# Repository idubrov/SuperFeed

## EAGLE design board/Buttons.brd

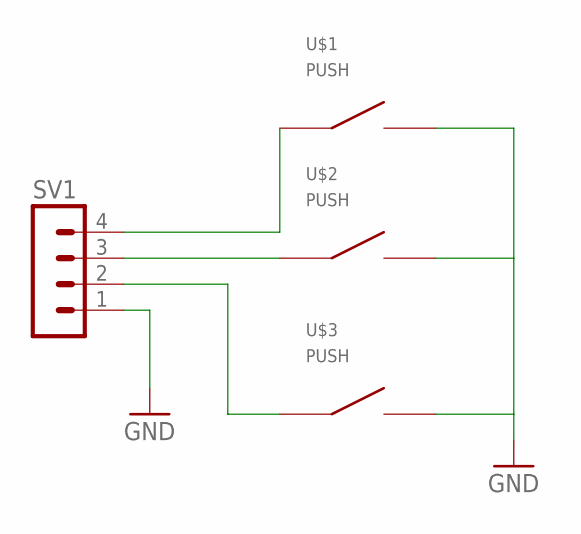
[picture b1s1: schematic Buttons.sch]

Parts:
SV1: MA04-1W
U$1, U$2, U$3: PUSH

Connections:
GND: SV1.1, U$1.3 (2), U$1.4 (2), U$2.3 (2), U$2.4 (2), U$3.3 (2), U$3.4 (2)
unnamed: SV1.2, U$3.1, U$3.2 (1)
unnamed: SV1.3, U$2.1, U$2.2 (1)
unnamed: SV1.4, U$1.1, U$1.2 (1)

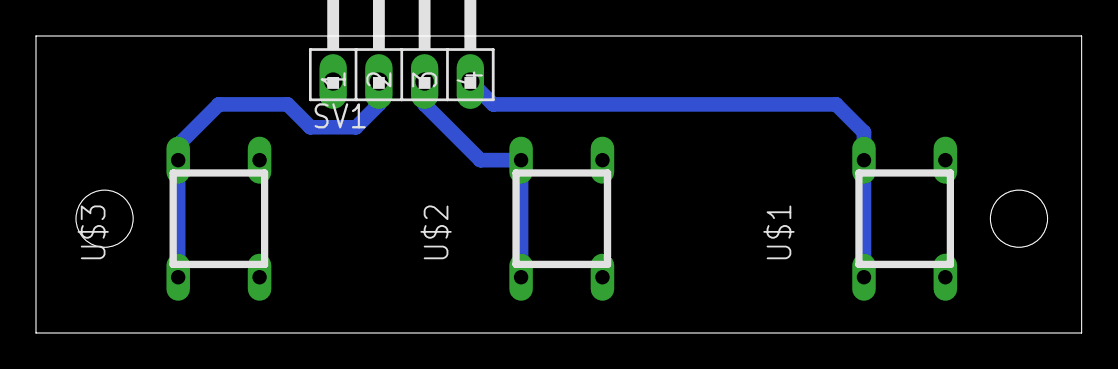
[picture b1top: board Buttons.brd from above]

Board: 2 copper layers, 58.1 x 16.5 mm, 4 parts (0 on the bottom side), 4 nets.

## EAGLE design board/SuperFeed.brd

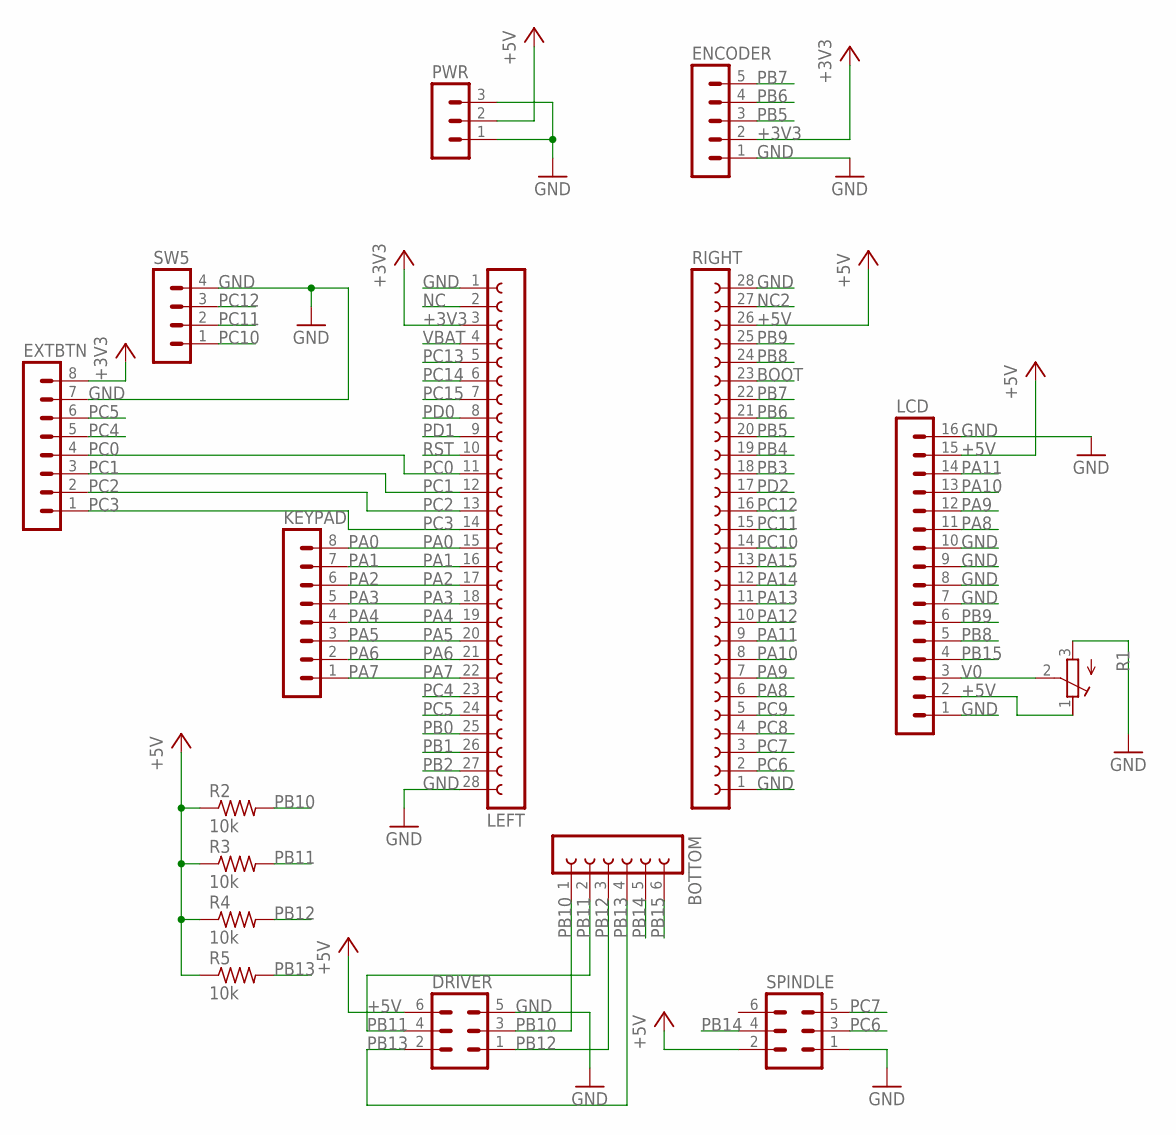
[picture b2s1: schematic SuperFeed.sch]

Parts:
BOTTOM: FE06-1; FE06
DRIVER: MA03-2W
ENCODER: MA05-1W
EXTBTN: MA08-1W
KEYPAD: MA08-1W
LCD: MA16-1
LEFT: FE28-1; FE28
PWR: MA03-1W
R1: R-TRIMMT93YA; RTRIMT93YA
R2, R3, R4, R5: 10k; 0207/10
RIGHT: FE28-1; FE28
SPINDLE: MA03-2W
SW5: MA04-1W

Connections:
+3V3: ENCODER.2, EXTBTN.8, LEFT.3
+5V: DRIVER.6, LCD.2, LCD.15, PWR.2, R1.1 (E), R2.1, R3.1, R4.1, R5.1, RIGHT.26, SPINDLE.2
BOOT: RIGHT.23
GND: DRIVER.5, ENCODER.1, EXTBTN.7, LCD.1, LCD.7, LCD.8, LCD.9, LCD.10, LCD.16, LEFT.1, LEFT.28, PWR.1, PWR.3, R1.3 (A), RIGHT.1, RIGHT.28, SPINDLE.1, SW5.4
NC: LEFT.2
NC2: RIGHT.27
PA0: KEYPAD.8, LEFT.15
PA1: KEYPAD.7, LEFT.16
PA2: KEYPAD.6, LEFT.17
PA3: KEYPAD.5, LEFT.18
PA4: KEYPAD.4, LEFT.19
PA5: KEYPAD.3, LEFT.20
PA6: KEYPAD.2, LEFT.21
PA7: KEYPAD.1, LEFT.22
PA8: LCD.11, RIGHT.6
PA9: LCD.12, RIGHT.7
PA10: LCD.13, RIGHT.8
PA11: LCD.14, RIGHT.9
PA12: RIGHT.10
PA13: RIGHT.11
PA14: RIGHT.12
PA15: RIGHT.13
PB0: LEFT.25
PB1: LEFT.26
PB2: LEFT.27
PB3: RIGHT.18
PB4: RIGHT.19
PB5: ENCODER.3, RIGHT.20
PB6: ENCODER.4, RIGHT.21
PB7: ENCODER.5, RIGHT.22
PB8: LCD.5, RIGHT.24
PB9: LCD.6, RIGHT.25
PB10: BOTTOM.1, DRIVER.3, R2.2
PB11: BOTTOM.2, DRIVER.4, R3.2
PB12: BOTTOM.3, DRIVER.1, R4.2
PB13: BOTTOM.4, DRIVER.2, R5.2
PB14: BOTTOM.5, SPINDLE.4
PB15: BOTTOM.6, LCD.4
PC0: EXTBTN.4, LEFT.11
PC1: EXTBTN.3, LEFT.12
PC2: EXTBTN.2, LEFT.13
PC3: EXTBTN.1, LEFT.14
PC4: EXTBTN.5, LEFT.23
PC5: EXTBTN.6, LEFT.24
PC6: RIGHT.2, SPINDLE.3
PC7: RIGHT.3, SPINDLE.5
PC8: RIGHT.4
PC9: RIGHT.5
PC10: RIGHT.14, SW5.1
PC11: RIGHT.15, SW5.2
PC12: RIGHT.16, SW5.3
PC13: LEFT.5
PC14: LEFT.6
PC15: LEFT.7
PD0: LEFT.8
PD1: LEFT.9
PD2: RIGHT.17
RST: LEFT.10
V0: LCD.3, R1.2 (S)
VBAT: LEFT.4

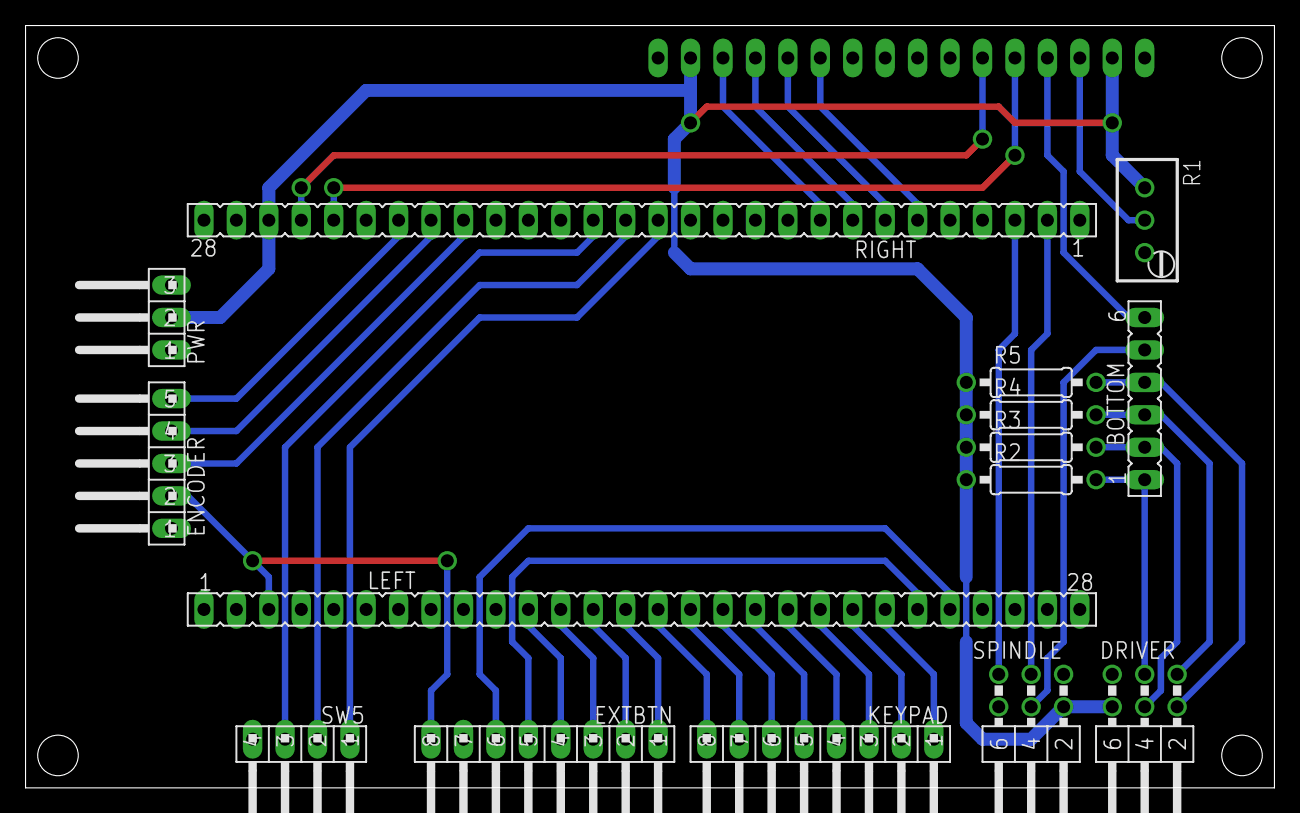
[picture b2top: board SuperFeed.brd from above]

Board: 2 copper layers, 97.8 x 59.7 mm, 16 parts (1 on the bottom side), 38 nets.

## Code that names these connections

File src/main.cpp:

#include "simstream.hpp"
#include "util.hpp"
#include "settings.hpp"

// Hardwre
#include "hw/buttons.hpp"
#include "hw/core.hpp"
#include "hw/driver.hpp"
#include "hw/eeprom.hpp"
#include "hw/encoder.hpp"
#include "hw/keypad.hpp"
#include "hw/lcd.hpp"
#include "hw/spindle.hpp"

// Text UI
#include "tui/console.hpp"
#include "tui/menu/controls.hpp"
#include "tui/menu/inputs.hpp"
#include "tui/menu/menu.hpp"
#include "tui/menu/sampler.hpp"
#include "tui/menu/limits.hpp"
#include "tui/menu/powerfeed.hpp"
#include "tui/menu/drvtest.hpp"

// Stepper
#include "stepper/stepper.hpp"

extern "C"
{
void SysTick_Handler();
void TIM1_UP_TIM16_IRQHandler(); // STEP pulse generation
void TIM7_IRQHandler(); // Input debouncing
void TIM1_BRK_TIM15_IRQHandler(); // Spindle index

extern unsigned int __eeprom_start;
extern unsigned int __eeprom_pages;
}

// First, enable clocks for utilized subsystems
class application
{
	friend void ::TIM1_UP_TIM16_IRQHandler();
	friend void ::TIM7_IRQHandler();
	friend void ::TIM1_BRK_TIM15_IRQHandler();
public:
	application() :
			// Columns start with pin PA0, rows start with PA4
			keypad(GPIOA, GPIO_PinSource0, GPIO_PinSource4),
			// PC10-PC12 should be connected to the first three output of three buttons.
			buttons(GPIOC, GPIO_PinSource10),
			// PB5 should be connected to encoder button, PB6 and PB7 to rotary encoder.
			encoder(GPIOB, TIM4, GPIO_Pin_5, GPIO_Pin_6 | GPIO_Pin_7),
			// LCD display, RS pin should be connected to PB15, R/W to PB8 and E to PB9
			// D4-D7 should be connected to PB8-PB15
			lcd(GPIOB, GPIO_Pin_15, GPIO_Pin_8, GPIO_Pin_9, GPIOA,
			GPIO_PinSource8, hw::lcd::Bit4, false),
			// Stepper driver, PB13 should be connected to STEP, PB12 to DIR,
			// PB11 to ENABLE and PB10 to RESET.
			// ENABLE and RESET are active high (i.e, driver is enabled when both are high).
			driver(GPIOB, GPIO_Pin_13, GPIO_Pin_12, GPIO_Pin_11, GPIO_Pin_10,
			TIM1),
			// Spindle index, PB14 should be connected to hall sensor or optical sensor
			spindle(TIM15,
			GPIOB, GPIO_Pin_14),
			// Use page 126 and 127 for persistent storage
			eeprom((uint32_t) &__eeprom_start, (uint32_t) &__eeprom_pages), stepper(
					eeprom, driver), console(lcd,
			TIM7, encoder, keypad, buttons), sampler(spindle), rotatetest(
					driver, stepper, eeprom)
	{
	}

	void setup()
	{
		RCC_APB2PeriphClockCmd(RCC_APB2Periph_GPIOA, ENABLE);
		RCC_APB2PeriphClockCmd(RCC_APB2Periph_GPIOB, ENABLE);
		RCC_APB2PeriphClockCmd(RCC_APB2Periph_GPIOC, ENABLE);
		RCC_APB2PeriphClockCmd(RCC_APB2Periph_TIM1, ENABLE); // Stepper
		RCC_APB2PeriphClockCmd(RCC_APB2Periph_TIM15, ENABLE); // Spindle index timer
		RCC_APB2PeriphClockCmd(RCC_APB2Periph_AFIO, ENABLE);
		RCC_APB1PeriphClockCmd(RCC_APB1Periph_TIM4, ENABLE); // Encoder
		RCC_APB1PeriphClockCmd(RCC_APB1Periph_TIM6, ENABLE); // Utility timer
		RCC_APB1PeriphClockCmd(RCC_APB1Periph_TIM7, ENABLE); // Debouncing timer

		// Remap TIM15 to use PB14 as CH1
		AFIO->MAPR2 |= AFIO_MAPR2_TIM15_REMAP;
		// XXX: The following line doesn't work with gcc optimizations
		//GPIO_PinRemapConfig(GPIO_Remap_TIM15, ENABLE);

		// Setup interrupt for pulse timer (TIM1)
		NVIC_InitTypeDef timerIT;
		timerIT.NVIC_IRQChannel = TIM1_UP_TIM16_IRQn;
		timerIT.NVIC_IRQChannelPreemptionPriority = 0;
		timerIT.NVIC_IRQChannelSubPriority = 1;
		timerIT.NVIC_IRQChannelCmd = ENABLE;
		NVIC_Init(&timerIT);

		// Setup interrupt for debounce timer (TIM7)
		timerIT.NVIC_IRQChannel = TIM7_IRQn;
		timerIT.NVIC_IRQChannelPreemptionPriority = 3; // lowest priority
		timerIT.NVIC_IRQChannelSubPriority = 3; // lowest priority
		timerIT.NVIC_IRQChannelCmd = ENABLE;
		NVIC_Init(&timerIT);

		// Setup interrupt for spindle index timer (TIM15)
		timerIT.NVIC_IRQChannel = TIM1_BRK_TIM15_IRQn;
		timerIT.NVIC_IRQChannelPreemptionPriority = 3;
		timerIT.NVIC_IRQChannelSubPriority = 2;
		timerIT.NVIC_IRQChannelCmd = ENABLE;
		NVIC_Init(&timerIT);

		// Setup core hardware (on-board LEDs and delay timer)
		hw::core::setup();

		// Setup all used hardware
		eeprom.initialize();
		keypad.initialize();
		buttons.initialize();
		encoder.initialize();
		lcd.initialize();
		lcd.display(hw::lcd::DisplayOn, hw::lcd::CursorOff, hw::lcd::BlinkOff);
		driver.initialize();
		spindle.initialize();
		console.initialize();

		stepper.reset();
	}

	void run()
	{
		using namespace tui;
		lcd.clear();
		auto main_menu = menu::create("Main menu", "ABC",
				menu::powerfeed(driver, stepper, spindle, eeprom),
				//menu::limits(eeprom),
				sampler, menu::inputs(),
				menu::create("Settings", "ABC",
						menu::create("Driver timings",
								menu::label("Timings (in nsec)"),
								menu::numeric(eeprom, settings::StepLen),
								menu::numeric(eeprom, settings::StepSpace),
								menu::numeric(eeprom, settings::DirectionSetup),
								menu::numeric(eeprom, settings::DirectionHold),
								menu::back()),
						menu::create("Stepper config",
								menu::toggle(eeprom, settings::Reverse),
								menu::spinner(eeprom, settings::Microsteps),
								menu::numeric(eeprom, settings::Acceleration),
								rotatetest,
								menu::toggle(eeprom, settings::MetricLeadscrew),
								menu::numeric(eeprom, settings::LeadscrewTPI),
								menu::numeric(eeprom, settings::LeadscrewPitch),
								menu::label("Gearing"),
								menu::numeric(eeprom, settings::LeadscrewGear),
								menu::numeric(eeprom, settings::StepperGear),
								menu::back()),
						menu::create("Feeds",
								menu::numeric(eeprom, settings::RapidFeed),
								menu::numeric(eeprom, settings::LastFeedIPM),
								menu::numeric(eeprom, settings::LastFeedIPR),
								menu::toggle(eeprom, settings::LastFeedMode),
								menu::back()), menu::erase_settings(eeprom),
						tui::menu::back()));
		main_menu.activate(console, 0);

////		// STEPPER.....
//		bool pressed = false;
//		uint8_t last = buttons::None;
//
//		uint32_t thread = 8; // TPI of the thread we are cutting
//		uint32_t RPM = 120 << 8; // Spindle speed in 24.8 format
//		uint32_t fast = ::cfg::stepper::StepsPerInch * RPM / (60 * thread); // steps per sec
//		uint32_t slow = fast / 3;
//
//		while (1)
//		{
//			lcd << lcd::position(0, 0) << stepper;
//
//			uint8_t pos = buttons.rawbuttons();
//			if (pos != last)
//			{
//				stepper.set_speed(pos == switch5::LL ? fast : slow);
//			}
//			last = pos;
//
//			if (encoder.raw_pressed())
//			{
//				if (!pressed)
//				{
//					stepper.move(1000);
//				}
//				pressed = true;
//			}
//			else
//			{
//				pressed = false;
//			}
//		}
//		while (1)
//			;
	}

	static application& instance()
	{
		return g_app;
	}
private:
	// Hardware
	hw::keypad keypad;
	hw::buttons buttons;
	hw::encoder encoder;
	hw::lcd::HD44780 lcd;
	hw::driver driver;
	hw::spindle spindle;
	hw::eeprom eeprom;

	// Stepper motor controller
	stepper::controller stepper;

	// TUI
	tui::console console;
	tui::menu::sampler sampler;
	tui::menu::rotatetest rotatetest;
private:
	static application g_app;
};

application application::g_app;

/**
 * @brief  Main program.
 * @param  None
 * @retval None
 */
int main()
{
	application::instance().setup();
	application::instance().run();
	return 0;
}

// IRQ handlers
extern "C" void __attribute__ ((section(".after_vectors")))
TIM1_UP_TIM16_IRQHandler()
{
	TIM_ClearITPendingBit(TIM1, TIM_IT_Update);
	application::instance().stepper.step_completed();
}

extern "C" void __attribute__ ((section(".after_vectors")))
TIM7_IRQHandler()
{
	TIM_ClearITPendingBit(TIM7, TIM_IT_Update);
	application::instance().console.debounce();
}

extern "C" void __attribute__ ((section(".after_vectors")))
TIM1_BRK_TIM15_IRQHandler()
{
	// Check flags before we act
	ITStatus update = TIM_GetITStatus(TIM15, TIM_IT_Update);
	ITStatus capture = TIM_GetITStatus(TIM15, TIM_IT_CC1);
	if (update)
	{
		TIM_ClearITPendingBit(TIM15, TIM_IT_Update);
		application::instance().spindle.overflow_handler();
	}
	if (capture)
	{
		TIM_ClearITPendingBit(TIM15, TIM_IT_CC1);
		application::instance().spindle.index_pulse_hanlder();

		// Spindle sampling
		application::instance().sampler.index_pulse_handler();
	}
}

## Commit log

2014-06-06 Creating new project template
    Using GNU ARM Eclipse plugin to create project template.
2014-06-06 Deleting diagnostic utilities
2014-06-06 __isr_vectors should be externally visible for LTO
    For link-time optimization, __isr_vectors should be marked
    as externally visible (so it is not "optimized" away.)
2014-06-06 Adding project initial content
2014-06-06 Creating Makefile
    Creating makefile for console builds
2014-06-06 Produce .bin files as part of IDE build
2014-06-06 .gitignore added
2014-06-06 Fixing compilation warning
2014-06-06 Fixing compilation warnings in vectors definition
    Do not declare vector handlers which are not applicable to current device
2014-06-06 Cleaning up unused code
2014-06-06 Need less NOPs since MCU is slower
2014-06-06 Fixing compilation warnings
2014-06-07 Adding two more goals to Makefile
2014-06-07 Stepper tester
2014-06-07 Removing file which changes every time
2014-06-07 Ignoring .settings
2014-06-07 Implementing support for tick function
2014-06-07 Started working on stepper control
2014-06-08 Checking switch
2014-06-08 Working on stepper driver
2014-06-08 Implementing software debouncer for 5-position switch
2014-06-08 Renaming sample so Eclipse doesn't try to parse it
2014-06-08 Reset switch position when initializing
2014-06-08 Configuring keypad
2014-06-09 Refactoring code
2014-06-10 Custom delegates
2014-06-10 Reworking delegates
2014-06-11 SysTick is managed by systick
2014-06-11 Removing unused timer
2014-06-11 Making keypad a normal class
2014-06-11 Use foreach
2014-06-12 Making LCD normal C++ class
2014-06-12 Disable SysTick interrupt in SysTick register
2014-06-12 Return key as character
2014-06-12 Debouncing for keypad
2014-06-12 Separating initialization from constructors
2014-06-13 Notes added
2014-06-13 Stepper timers
2014-06-13 Added notes
2014-06-13 Unused namespace usage removed
2014-06-13 Adding DMA to the project
2014-06-13 Using DMA for reloading timer
2014-06-13 DMA half-transfer and transfer handling
2014-06-14 Fixes
2014-06-14 Improved DMA control
2014-06-14 Minor
2014-06-14 Use bitbanding
2014-06-14 PWM + BitBanding
2014-06-14 Code cleanup
2014-06-14 Experimenting with second start
2014-06-14 fixing spurious DMA transfer
2014-06-15 Using circular buffer
2014-06-15 Use HT interrupt
2014-06-15 Fixing issues with interrupts clearing
2014-06-17 Working on simple streams lib
2014-06-17 Working on number printing
2014-06-17 Fixing reset handler
2014-06-17 Using fancy LCD API
2014-06-17 Use ARR preload instead of DMA
2014-06-17 Extracting configuration objects
2014-06-17 Adding pre-calculated limits
2014-06-17 Adjusting timer
2014-06-17 Simplifying code to use one timer for STEP
2014-06-18 Minor documentation update
2014-06-18 Don't preload CC bits, preload CC1 register
2014-06-19 Fixing PWM configuration
2014-06-19 Ramp generation
2014-06-19 Working on step generation
2014-06-19 Cleaning up stepgen
2014-06-19 Cleanup
2014-06-20 Working on stopping of stepgen
2014-06-20 Minimal movement implementation
2014-06-20 Do not recalculate denominator when decelerating
2014-06-20 Refactoring stepgen
2014-06-20 Refactoring
2014-06-21 Support for setting target speed/step for the stepgen
2014-06-21 Working on stepper controller
2014-06-21 Reset slewing if target speed is changed
2014-06-21 Code cleanup, wait for interrupt to clear when starting move
2014-06-21 Should load idle values when timer is about to stop
2014-06-23 Working on alternate mappings
2014-06-25 Alternate mapping
2014-06-25 Documenting new breakout board design
2014-06-25 According to datasheet, shouldn't use pull-up resistors on 5V input
2014-06-25 Created Eagle CAD board
2014-06-25 Connect third pin to ground on power connector
2014-06-25 Rotating board to fit into 80x100mm limitation
2014-06-26 Adding extra buttons on board
2014-06-26 Updating
2014-06-26 Reducing amount of different hole sizes
2014-06-26 Ignore temporary files
2014-06-26 Minor changes to pad geometry
2014-06-26 Updating test board
2014-06-26 Minor improvement in the board
2014-06-26 Turning orphans to off
2014-06-27 Started working on EEPROM emulation
2014-06-27 Working on EEPROM emulation
2014-06-27 Fixing bug in rescue logic
2014-06-27 Two more pins on extension connector
2014-06-28 Check both tag and data
2014-06-28 Working on simple menu implementation
2014-06-29 Experimenting with text ui
2014-06-29 Show position with cursor
2014-06-29 Adjustments for better routing properties
2014-06-30 Re-routing board to use GND plane on bottom side
2014-06-30 Custom design rules, moving pot a little bit
2014-07-02 Minor improvements to the board
2014-07-02 Making wire thicker
2014-07-02 Minor change
2014-07-03 Wire colors
2014-07-03 Updating for latest board
2014-07-03 Support for 4-bit mode LCD
2014-07-03 In 4-bit mode we only need to initialize 4 pins
2014-07-03 Inverting switch positions
2014-07-03 Configuring stepper to use open-drain and CH1N
2014-07-03 More tests
2014-07-03 Reorganizing sources
2014-07-03 Temporarily removing debouncing
2014-07-04 Working on debouncing
2014-07-04 Use timer for debouncing
2014-07-04 Getting rid of delegates & systick support
2014-07-04 Use ldscripts for defining EEPROM location and size
2014-07-04 Pull columns down (same direction as user button PB3 pulls) instead of up
2014-07-04 RAI for setting encoder limit
2014-07-04 Adding LCD reference to console class
2014-07-04 Renaming input.cpp into console.cpp, moving console into namespace tui
2014-07-04 Automatic console state management
2014-07-04 Verifying automatic encoder state management works
2014-07-07 Minor cleanup
2014-07-07 Refactoring console implementation
2014-07-08 Replacing switch5 with three buttons
2014-07-08 Minor refactoring
2014-07-08 Don't need to generate eeprom section
2014-07-08 Started working on spindle index pulse
2014-07-08 gnu11 -> c11
2014-07-09 Spindle interrupts
2014-07-09 Moving settings.cpp into menu/
2014-07-09 Working on spindle speed/index
2014-07-09 Implementing RPM sampler
2014-07-09 Fixing bug in spindle
2014-07-09 Working on sampler
2014-07-09 Removing usages of 'volatile'
2014-07-10 Fixing bugs introduced by storage size refactorings
2014-07-10 Minor tweaks to the sampler
2014-07-10 UI to test inputs
2014-07-10 Minor ui improvements
2014-07-10 Experimenting with compile-time menus
2014-07-10 Experimenting with variadic templates
2014-07-10 Using tuple from the std
2014-07-11 Extracting tuple applicator
2014-07-11 Working on menu implementation
2014-07-11 Fixing LCD busy flag in 4-bit mode
2014-07-11 Explicitly not using BF
2014-07-11 Fancier menu
2014-07-11 Adding _cxx.cpp to the build
2014-07-11 Refactoring menu implementation. Not using compile-time tricks
2014-07-11 Minor text change
2014-07-11 Let's try our luck with compile-time menu again
2014-07-11 Refactoring menu
2014-07-11 Working on menu
2014-07-12 Using array initializer to clean the buffer
2014-07-12 Fixing overflow bug
2014-07-12 Fixing bug in tuple applicator
2014-07-12 Preserve capture size in sampler
2014-07-15 Don't get crazy with static checks. Implementing 'back' menu action
2014-07-15 Deleting old settings menu
2014-07-15 Implementing simple spinner control
2014-07-16 Working on a spinner
2014-07-16 Added item to erase eeprom settings
2014-07-16 Adding missing return statement
2014-07-16 Working on settings
2014-07-16 Started working on stepper delays configuration
2014-07-16 Working on delay settings
2014-07-16 More configurable settings
2014-07-16 Implementing boolean settings toggle control
2014-07-16 Started working on keypad-based numeric input
2014-07-16 Keypad-based input of numbers
2014-07-16 Fixing bugs in keypad numeric input
2014-07-16 Minor tweak
2014-07-17 Fixing bugs
2014-07-17 Fixing input bugs
2014-07-17 Minor corrections
2014-07-17 Started working on limits stats menu
2014-07-17 Working on the stepper controller
2014-07-18 Working on simple powerfeed
2014-07-22 Working on buttons board
2014-08-07 Updated board.md
2014-08-11 Updating Board.md
2014-08-12 Adding test functionality to the settings menu
2014-08-12 Merging encoder button and select button
2014-08-12 Pulling down encoder input
2014-08-17 Working on powerfeed
2014-08-17 Better number formatting
2014-08-17 fixing potential bug
2014-08-17 Fixing stepgen when first step is faster than desired speed
2014-08-17 Fixing overflow
2014-08-17 Fixing makefile
2014-08-17 Use 16.16 format for intermediate delay representation
2014-08-17 Always set direction
2014-08-18 Reload settings when entering powerfeed menu
2014-08-18 Allow reversing direction
2014-08-18 Fixing bug in menu
2014-08-18 Allow exiting from the menu by pressing '#'
2014-08-18 Support for hotkeys
2014-08-18 Initialize keypad current state properly
2014-08-18 Ranged value
2014-08-18 Reworking encoder
2014-08-19 Rapid traversals
2014-08-19 Allow zeroing position
2014-08-19 Allow changing spinner values by pressing arrow keys
2014-08-19 Menu consistency
2014-08-20 Allow positioning
2014-08-21 IPR mode, better UI for feed
2014-08-21 IPR mode
2014-08-21 Fixing spindle capture
2014-08-29 Filtering spindle input
2014-08-30 Fixing conflicting ids for settings, updating default values
